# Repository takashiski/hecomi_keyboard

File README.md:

# Hecomi keyboard

This keyboard is based HHKB pro 2 layout.

I have designed this keyboard hecomi want. So this keyboard is "Hecomi Happy Keyboard" :).

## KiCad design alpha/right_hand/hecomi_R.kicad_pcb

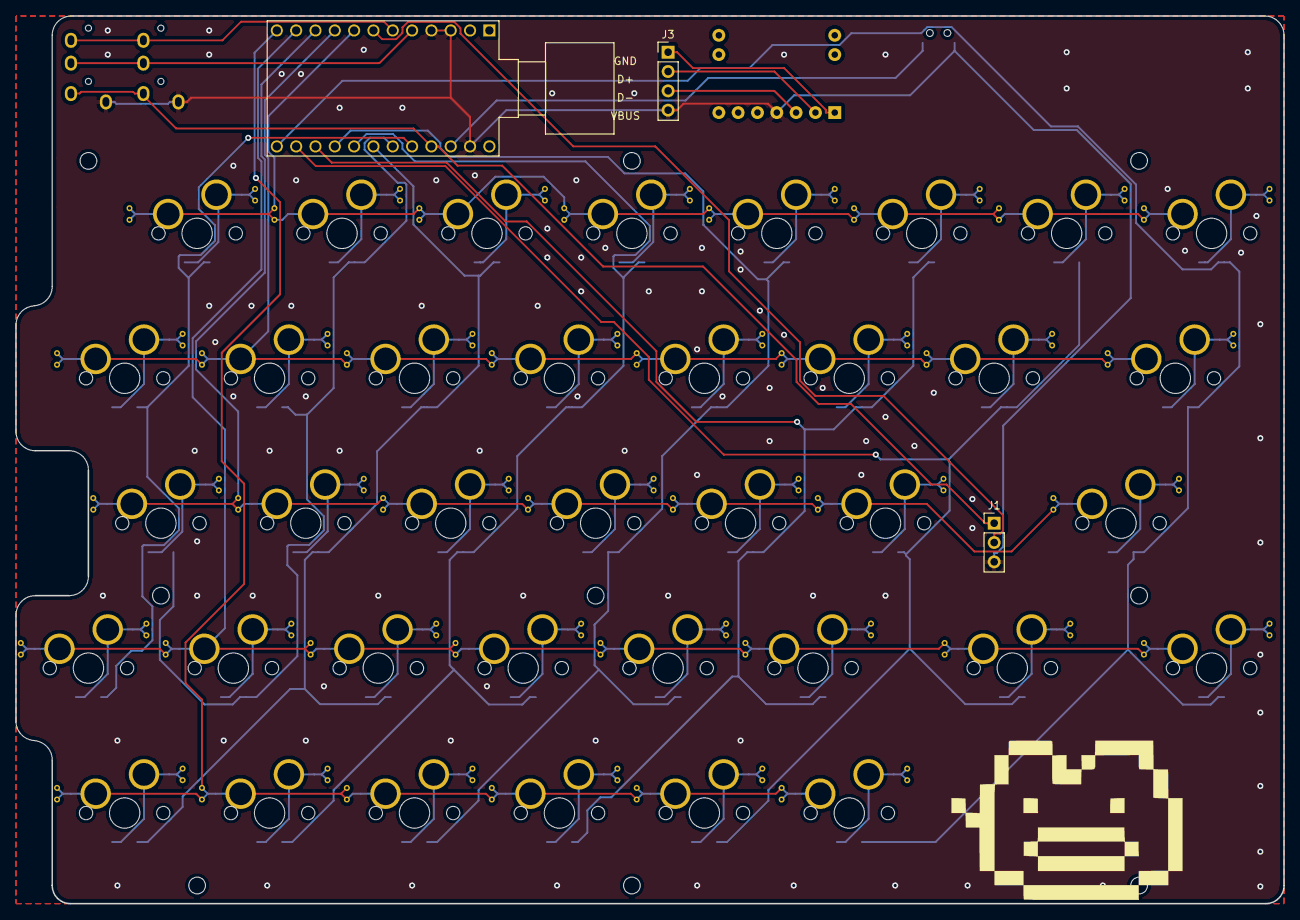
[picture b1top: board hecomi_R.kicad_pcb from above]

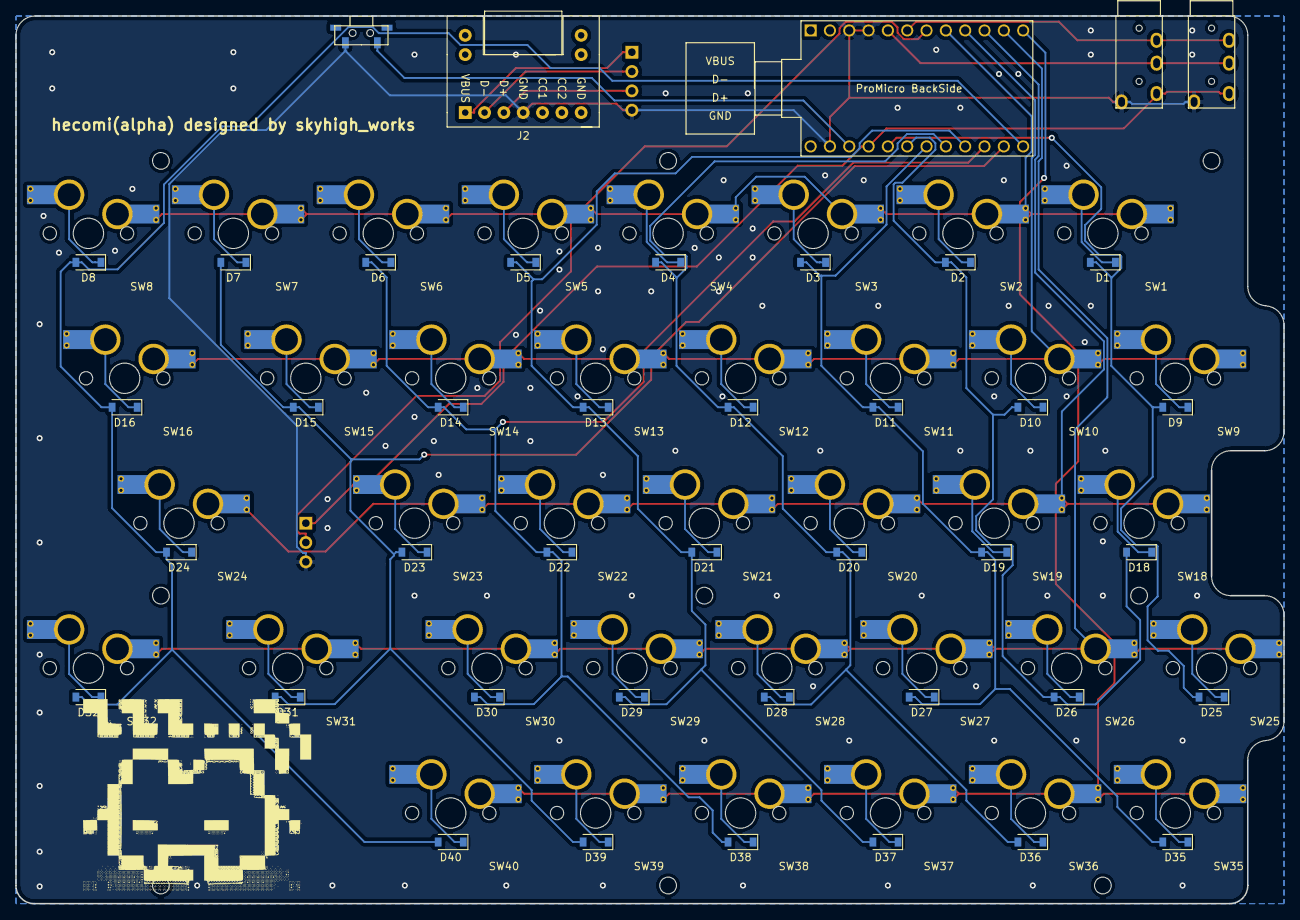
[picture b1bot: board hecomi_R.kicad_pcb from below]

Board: 2 copper layers, 166.7 x 116.7 mm, 92 parts (41 on the bottom side), 59 nets.

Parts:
D1, D2, D3, D4, D5, D6, D7, D8, D9, D10, D11, D12, D13, D14, D15, D16, D18, D19, D20, D21, D22, D23, D24, D25, D26, D27, D28, D29, D30, D31, D32, D35, D36, D37, D38, D39, D40: D; D_SOD-123
J1: Conn_01x03_Female; PinHeader_1x03_P2.54mm_Vertical
J2: Conn_01x07_Female; usb_type-c_akitsuki
J3: Conn_01x04_Female; PinHeader_1x04_P2.54mm_Vertical
J4, J5: Conn_01x04_Female; TRRS-PJ-320A
LOGO1: LOGO; hecomi_bmp
LOGO2: LOGO; hecomiP_bmp
MH1, MH2, MH3, MH4, MH5, MH6, MH7, MH8, MH9: MountingHole; MountingHole_2.2mm_M2
SW1, SW2, SW3, SW4, SW5, SW6, SW7, SW8, SW9, SW10, SW11, SW12, SW13, SW14, SW15, SW16, SW18, SW19, SW20, SW21, SW22, SW23, SW24, SW25, SW26, SW27, SW28, SW29, SW30, SW31, SW32, SW35, SW36, SW37, SW38, SW39, SW40: SW_Push; MXOnly-1U-Hotswap-Antishear
SW41: SW_Push; 1101VS-E
U1: ProMicro PartsSide; ProMicro

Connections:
COL0: D1.2, D9.2, D25.2, U1.20
COL1: D2.2, D10.2, D18.2, D26.2, U1.19
COL2: D3.2, D11.2, D19.2, D27.2, D35.2, U1.18
COL3: D4.2, D12.2, D20.2, D28.2, D36.2, U1.17
COL4: D5.2, D13.2, D21.2, D29.2, D37.2, U1.16
COL5: D6.2, D14.2, D22.2, D30.2, D38.2, U1.15
COL6: D7.2, D15.2, D23.2, D31.2, D39.2, U1.14
COL7: D8.2, D16.2, D24.2, D32.2, D40.2, U1.13
D+: J2.3, J3.3
D-: J2.2, J3.2
GND: J1.3, J2.4, J3.4, J4.1, J5.1, SW41.2, U1.3, U1.4, U1.23
LED: J1.2, U1.7
unnamed: D1.1, SW1.2
unnamed: D2.1, SW2.2
unnamed: D3.1, SW3.2
unnamed: D4.1, SW4.2
unnamed: D5.1, SW5.2
unnamed: D6.1, SW6.2
unnamed: D7.1, SW7.2
unnamed: D8.1, SW8.2
unnamed: D9.1, SW9.2
unnamed: D10.1, SW10.2
unnamed: D11.1, SW11.2
unnamed: D12.1, SW12.2
unnamed: D13.1, SW13.2
unnamed: D14.1, SW14.2
unnamed: D15.1, SW15.2
unnamed: D16.1, SW16.2
unnamed: D18.1, SW18.2
unnamed: D19.1, SW19.2
unnamed: D20.1, SW20.2
unnamed: D21.1, SW21.2
unnamed: D22.1, SW22.2
unnamed: D23.1, SW23.2
unnamed: D24.1, SW24.2
unnamed: D25.1, SW25.2
unnamed: D26.1, SW26.2
unnamed: D27.1, SW27.2
unnamed: D28.1, SW28.2
unnamed: D29.1, SW29.2
unnamed: D30.1, SW30.2
unnamed: D31.1, SW31.2
unnamed: D32.1, SW32.2
unnamed: D35.1, SW35.2
unnamed: D36.1, SW36.2
unnamed: D37.1, SW37.2
unnamed: D38.1, SW38.2
unnamed: D39.1, SW39.2
unnamed: D40.1, SW40.2
ROW0: SW1.1, SW2.1, SW3.1, SW4.1, SW5.1, SW6.1, SW7.1, SW8.1, U1.8
ROW1: SW9.1, SW10.1, SW11.1, SW12.1, SW13.1, SW14.1, SW15.1, SW16.1, U1.9
ROW2: SW18.1, SW19.1, SW20.1, SW21.1, SW22.1, SW23.1, SW24.1, U1.10
ROW3: SW25.1, SW26.1, SW27.1, SW28.1, SW29.1, SW30.1, SW31.1, SW32.1, U1.11
ROW4: SW35.1, SW36.1, SW37.1, SW38.1, SW39.1, SW40.1, U1.12
RST: SW41.1, U1.22
SCL: J4.3, J5.3, U1.5
SDA: J4.4, J5.4, U1.6
VBUS: J2.1, J3.1
VCC: J1.1, J4.2, J5.2, U1.21

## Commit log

2018-12-03 init
2018-12-03 remove swap file
2019-02-24 add alpha
2019-02-24 remove moved files
2019-02-26 grouped
2019-02-26 add plate SVG
2019-02-26 add plate CDR file for multi print on 450x300mm
